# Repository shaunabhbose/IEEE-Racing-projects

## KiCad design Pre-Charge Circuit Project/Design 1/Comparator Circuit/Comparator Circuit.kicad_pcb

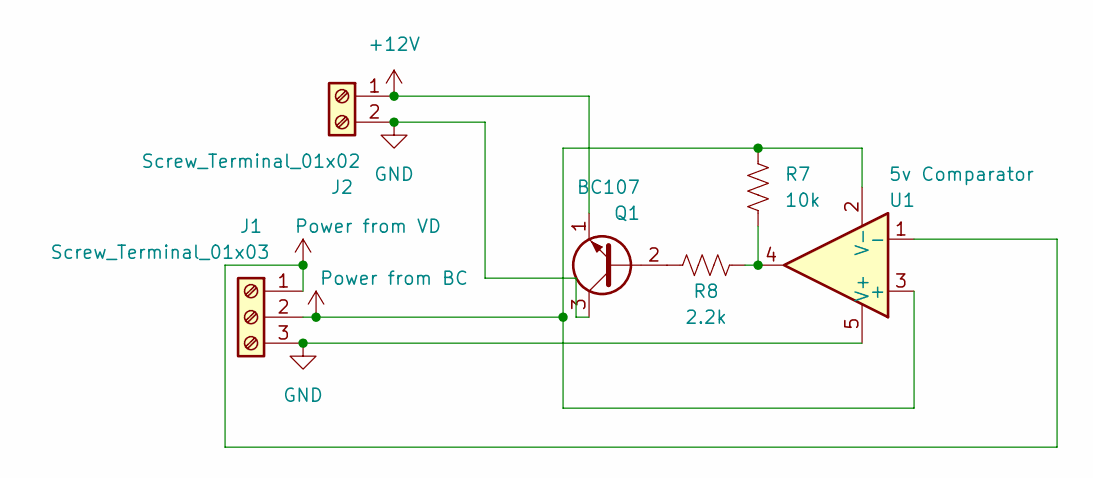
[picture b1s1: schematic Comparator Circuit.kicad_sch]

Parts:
J1: Screw_Terminal_01x03; TerminalBlock_MaiXu_MX126-5.0-03P_1x03_P5.00mm
J2: Screw_Terminal_01x02; TerminalBlock_MaiXu_MX126-5.0-02P_1x02_P5.00mm
Q1: BC107; TO-18-3
R7: 10k; R_Axial_DIN0204_L3.6mm_D1.6mm_P7.62mm_Horizontal
R8: 2.2k; R_Axial_DIN0204_L3.6mm_D1.6mm_P7.62mm_Horizontal
U1: 5v Comparator; SOT-23-5

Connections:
+12V: J2.1, Q1.1 (E)
GND: J1.3, J2.2, Q1.3 (C), U1.5 (V+)
unnamed: Q1.2 (B), R8.1
unnamed: R7.2, R8.2, U1.4
Power from BC: J1.2, R7.1, U1.2 (V-), U1.3 (+)
Power from VD: J1.1, U1.1 (-)

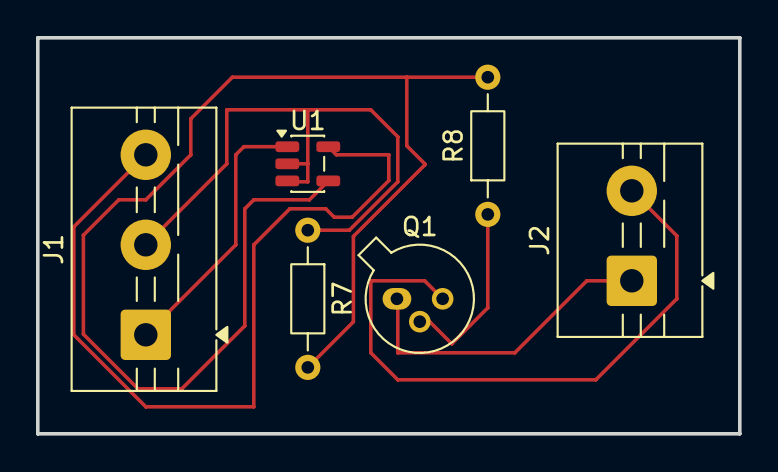
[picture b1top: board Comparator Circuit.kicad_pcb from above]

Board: 2 copper layers, 39.0 x 22.0 mm, 6 parts (0 on the bottom side), 6 nets.

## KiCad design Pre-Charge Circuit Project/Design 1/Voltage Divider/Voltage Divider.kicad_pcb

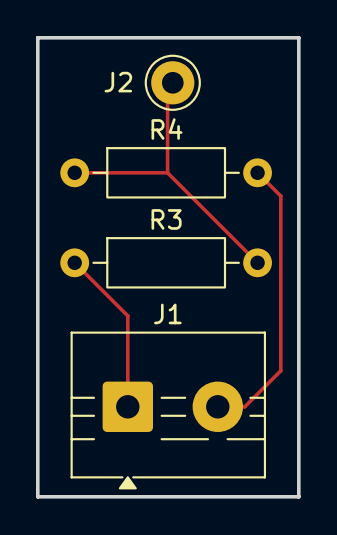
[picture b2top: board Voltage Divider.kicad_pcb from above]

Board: 2 copper layers, 14.5 x 25.5 mm, 4 parts (0 on the bottom side), 3 nets.

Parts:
J1: Screw_Terminal_01x02; TerminalBlock_MaiXu_MX126-5.0-02P_1x02_P5.00mm
J2: Conn_01x01_Pin; Pin_D1.0mm_L10.0mm_LooseFit
R3: 190k; R_Axial_DIN0207_L6.3mm_D2.5mm_P10.16mm_Horizontal
R4: 10k; R_Axial_DIN0207_L6.3mm_D2.5mm_P10.16mm_Horizontal

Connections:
unnamed: J1.1, R3.1
unnamed: J1.2, R4.2
Power from Voltage Divider: J2.1, R3.2, R4.1

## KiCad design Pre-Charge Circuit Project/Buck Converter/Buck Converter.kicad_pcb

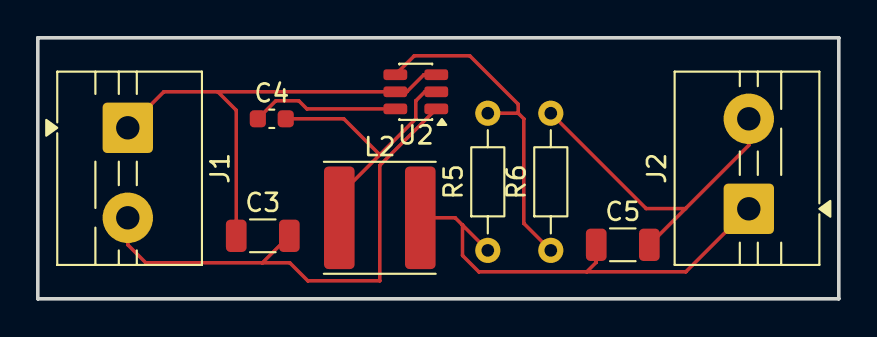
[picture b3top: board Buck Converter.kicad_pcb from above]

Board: 2 copper layers, 44.5 x 14.5 mm, 9 parts (0 on the bottom side), 7 nets.

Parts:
C3: 10muf; C_1206_3216Metric
C4: 0.1mu; C_0603_1608Metric
C5: 22mu; C_1206_3216Metric
J1, J2: Screw_Terminal_01x02; TerminalBlock_MaiXu_MX126-5.0-02P_1x02_P5.00mm
L2: 22mu; L_APV_ANR6028
R5: 100k; R_Axial_DIN0204_L3.6mm_D1.6mm_P7.62mm_Horizontal
R6: 13.3k; R_Axial_DIN0204_L3.6mm_D1.6mm_P7.62mm_Horizontal
U2: TPS54202DDC; SOT-23-6

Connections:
unnamed: C3.1, J1.1, U2.3 (VIN), U2.5 (EN)
unnamed: C3.2, J1.2, U2.1 (GND)
unnamed: C5.1, J2.1, L2.2, R5.2
unnamed: C5.2, J2.2, R6.2
unnamed: C4.1, U2.6 (BOOT)
unnamed: R5.1, R6.1, U2.4 (FB)
unnamed: C4.2, L2.1, U2.2 (SW)

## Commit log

2026-02-05 Added KiCad files from local disk
2026-02-06 add pics and rearrange files
2026-02-27 Create PreCharge Circuit Project
2026-02-27 Rearranged files to prechargecircuit project
2026-02-28 Added Image files and rearranged files
2026-06-07 Sorted files into designs 1 and 2
